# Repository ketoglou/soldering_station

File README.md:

# Soldering_station
A personal soldering station for Hakko 907 in Greek language but it can be easily adapted to any language.\
The following image shows the Temperature(red line) vs Resistance(blue line) chart of Hakko 907.\
 \
The equation that is used to calculate temperature is based in least squares method and \
it is the following : Temperature = 5.95 * Resistance - 281.3.

- PCB.zip : Contains gerber files for PCB.
- Firmware : Contains PIC18F27K42 firmware.

The following image shows the PCB.\

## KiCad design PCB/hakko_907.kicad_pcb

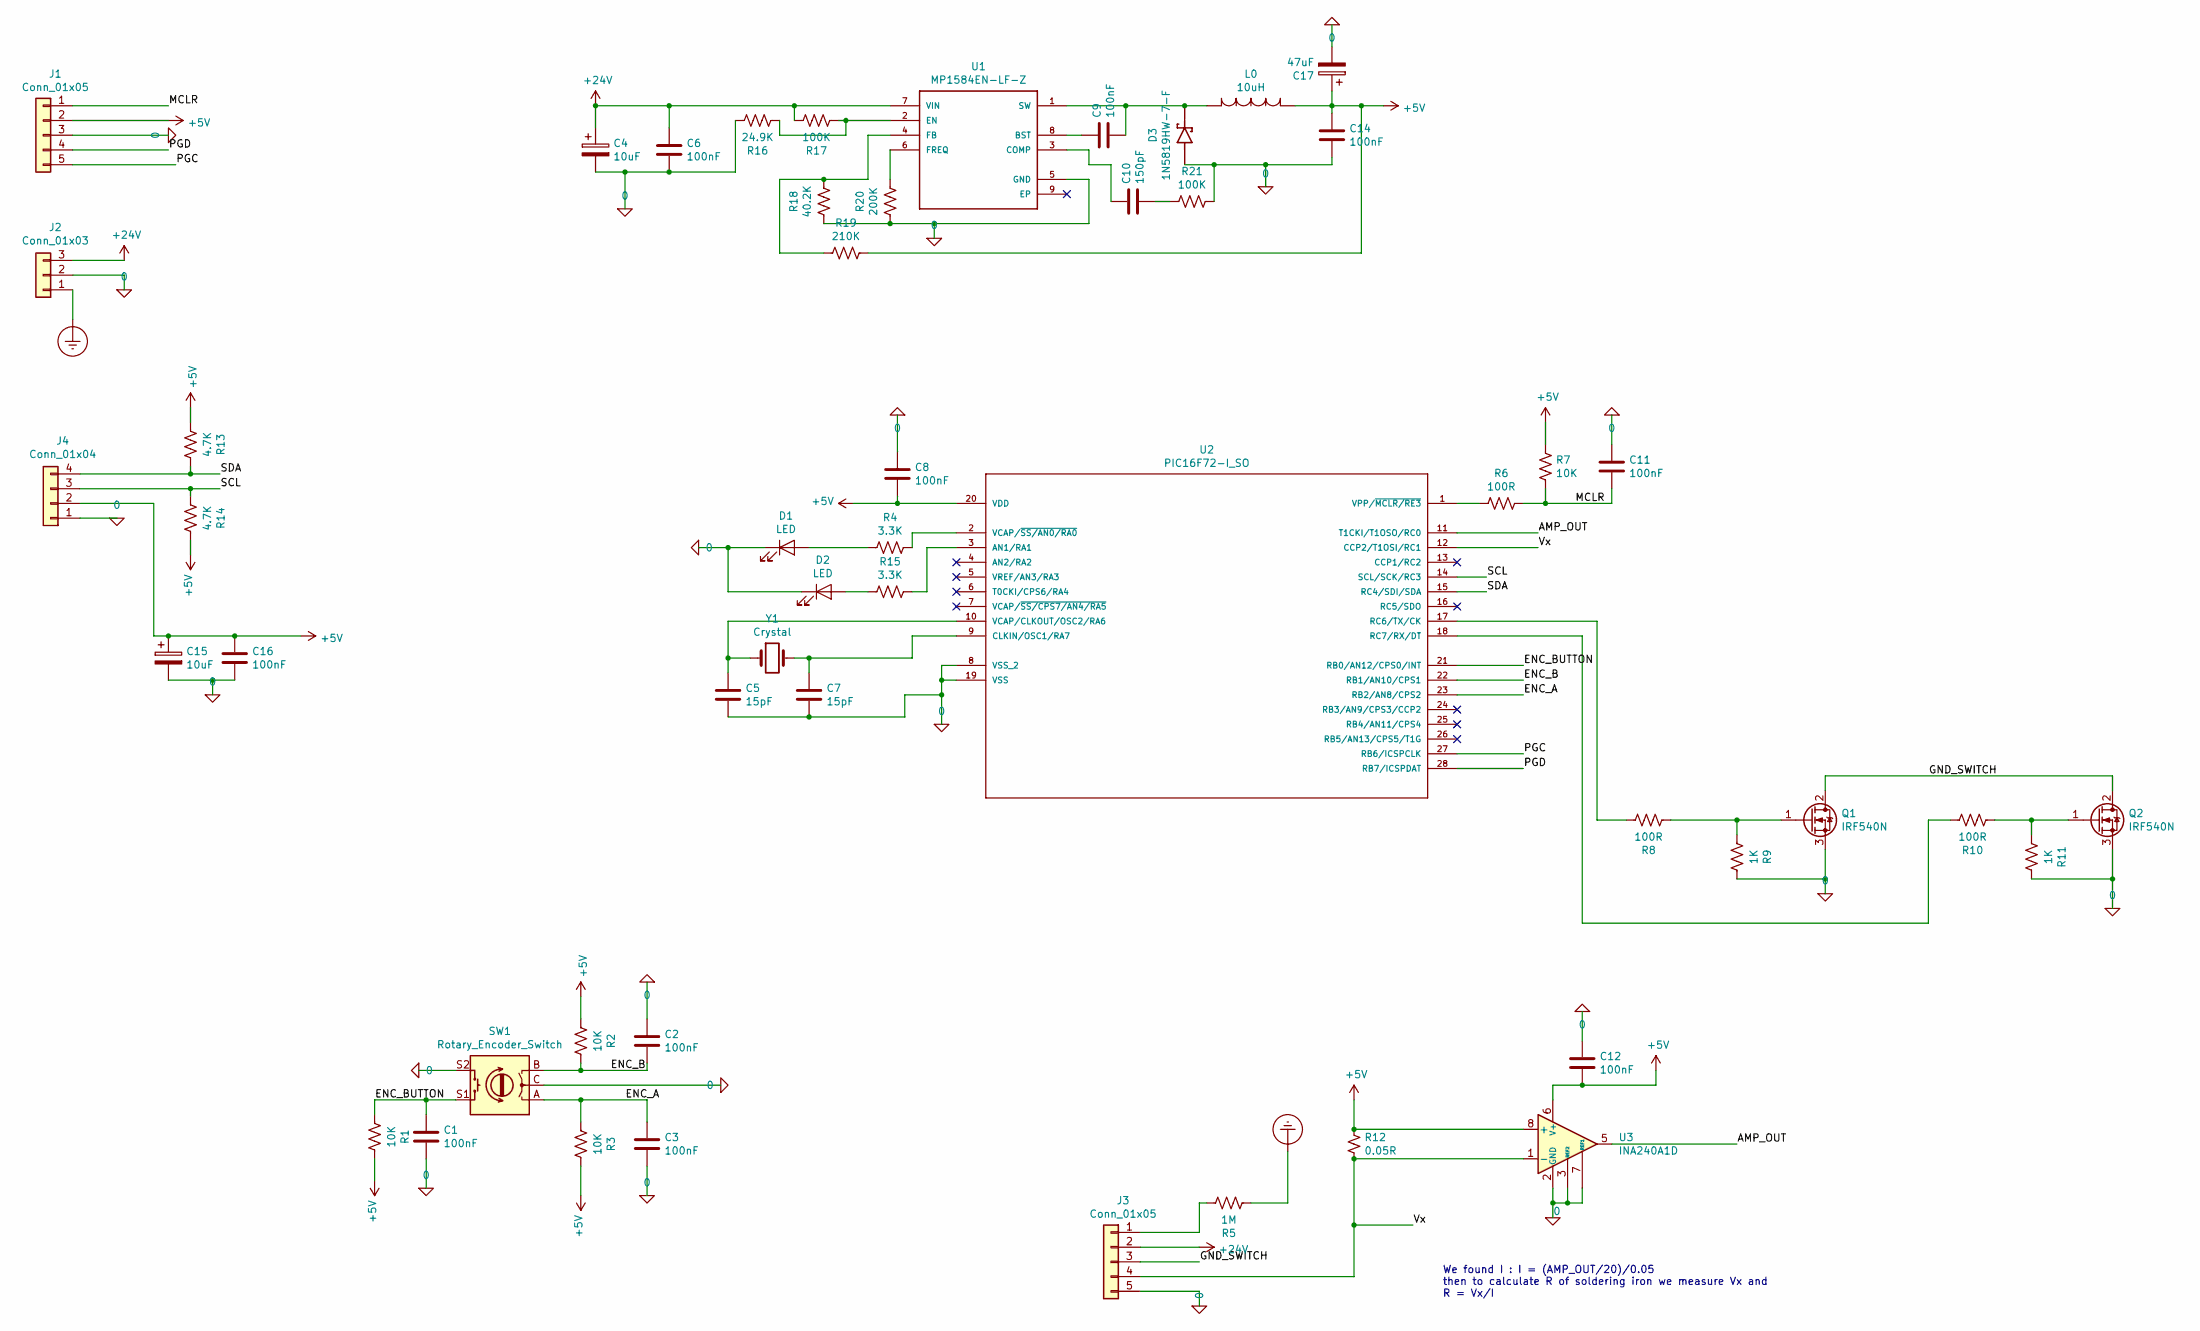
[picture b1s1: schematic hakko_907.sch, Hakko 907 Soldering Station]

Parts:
C1, C2, C3, C6, C8, C9, C11, C12, C14, C16: 100nF; C_0603_1608Metric_Pad1.05x0.95mm_HandSolder
C4, C15: 10uF; CP_Elec_8x6.2
C5, C7: 15pF; C_0603_1608Metric_Pad1.05x0.95mm_HandSolder
C10: 150pF; C_0603_1608Metric_Pad1.05x0.95mm_HandSolder
C17: 47uF; CP_Elec_6.3x5.9
D1, D2: LED; LED_0603_1608Metric_Pad1.05x0.95mm_HandSolder
D3: 1N5819HW-7-F; SOD3715X145N
J1, J3: Conn_01x05; PinHeader_1x05_P2.54mm_Vertical
J2: Conn_01x03; PinHeader_1x03_P2.54mm_Vertical
J4: Conn_01x04; PinHeader_1x04_P2.54mm_Vertical
L0: 10uH; INDM7676X355N
Q1, Q2: IRF540N; TO-220-3_Vertical
R1, R2, R3, R7: 10K; R_0603_1608Metric_Pad1.05x0.95mm_HandSolder
R4, R15: 3.3K; R_0603_1608Metric_Pad1.05x0.95mm_HandSolder
R5: 1M; R_Axial_DIN0309_L9.0mm_D3.2mm_P20.32mm_Horizontal
R6, R8, R10: 100R; R_0603_1608Metric_Pad1.05x0.95mm_HandSolder
R9, R11: 1K; R_0603_1608Metric_Pad1.05x0.95mm_HandSolder
R12: 0.05R; R_2512_6332Metric_Pad1.52x3.35mm_HandSolder
R13, R14: 4.7K; R_0603_1608Metric_Pad1.05x0.95mm_HandSolder
R16: 24.9K; R_0603_1608Metric_Pad1.05x0.95mm_HandSolder
R17, R21: 100K; R_0603_1608Metric_Pad1.05x0.95mm_HandSolder
R18: 40.2K; R_0603_1608Metric_Pad1.05x0.95mm_HandSolder
R19: 210K; R_0603_1608Metric_Pad1.05x0.95mm_HandSolder
R20: 200K; R_0603_1608Metric_Pad1.05x0.95mm_HandSolder
SW1: Rotary_Encoder_Switch; RotaryEncoder_Alps_EC11E-Switch_Vertical_H20mm
U1: MP1584EN-LF-Z; SOIC127P600X170-9N
U2: PIC16F72-I_SO; SOIC127P1030X265-28N
U3: INA240A1D; SOIC-8_3.9x4.9mm_P1.27mm
Y1: Crystal; Crystal_HC49-4H_Vertical

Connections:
0: C1.2, C2.1, C3.2, C4.2, C5.2, C6.2, C7.2, C8.1, C11.1, C12.1, C14.2, C15.2, C16.2, C17.2, D1.1 (K), D2.1 (K), D3.A, J1.3, J2.2, J3.5, J4.1, Q1.3 (S), Q2.3 (S), R9.1, R11.1, R16.1, R18.2, R20.2, R21.1, SW1.C, SW1.S2, U1.5 (GND), U2.8 (VSS_2), U2.19 (VSS), U3.2 (GND), U3.3 (REF2), U3.4 (GND), U3.7 (REF1)
+5V: C8.2, C12.2, C14.1, C15.1, C16.1, C17.1, J1.2, J4.2, L0.1, R1.1, R2.2, R3.1, R7.1, R12.1, R13.2, R14.1, R19.1, U2.20 (VDD), U3.6 (V+), U3.8 (+)
+24V: C4.1, C6.1, J2.3, J3.2, R17.1, U1.7 (VIN)
/AMP_OUT: U2.11 (T1CKI/T1OSO/RC0), U3.5
/ENC_A: C3.1, R3.2, SW1.A, U2.23 (RB2/AN8/CPS2)
/ENC_B: C2.2, R2.1, SW1.B, U2.22 (RB1/AN10/CPS1)
/ENC_BUTTON: C1.1, R1.2, SW1.S1, U2.21 (RB0/AN12/CPS0/INT)
/GND_SWITCH: J3.3, Q1.2 (D), Q2.2 (D)
/MCLR: C11.2, J1.1, R6.1, R7.2
/PGC: J1.5, U2.27 (RB6/ICSPCLK)
/PGD: J1.4, U2.28 (RB7/ICSPDAT)
/SCL: J4.3, R14.2, U2.14 (SCL/SCK/RC3)
/SDA: J4.4, R13.1, U2.15 (RC4/SDI/SDA)
/Vx: J3.4, R12.2, U2.12 (CCP2/T1OSI/RC1), U3.1 (-)
Earth_Protective: J2.1, R5.2
unnamed: C5.1, U2.10 (VCAP/CLKOUT/OSC2/RA6), Y1.1
unnamed: C7.1, U2.9 (CLKIN/OSC1/RA7), Y1.2
unnamed: C9.1, U1.8 (BST)
unnamed: C9.2, D3.C (K), L0.2, U1.1 (SW)
unnamed: C10.1, U1.3 (COMP)
unnamed: C10.2, R21.2
unnamed: D1.2 (A), R4.2
unnamed: D2.2 (A), R15.2
unnamed: J3.1, R5.1
unnamed: Q1.1 (G), R8.2, R9.2
unnamed: Q2.1 (G), R10.2, R11.2
unnamed: R4.1, U2.2 (VCAP/~SS/AN0/RA0)
unnamed: R6.2, U2.1 (VPP/~MCLR/RE3)
unnamed: R8.1, U2.17 (RC6/TX/CK)
unnamed: R10.1, U2.18 (RC7/RX/DT)
unnamed: R15.1, U2.3 (AN1/RA1)
unnamed: R16.2, R17.2, U1.2 (EN)
unnamed: R18.1, R19.2, U1.4 (FB)
unnamed: R20.1, U1.6 (FREQ)

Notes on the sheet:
We found I : I = (AMP_OUT/20)/0.05 then to calculate R of soldering iron we measure Vx and R = Vx/I

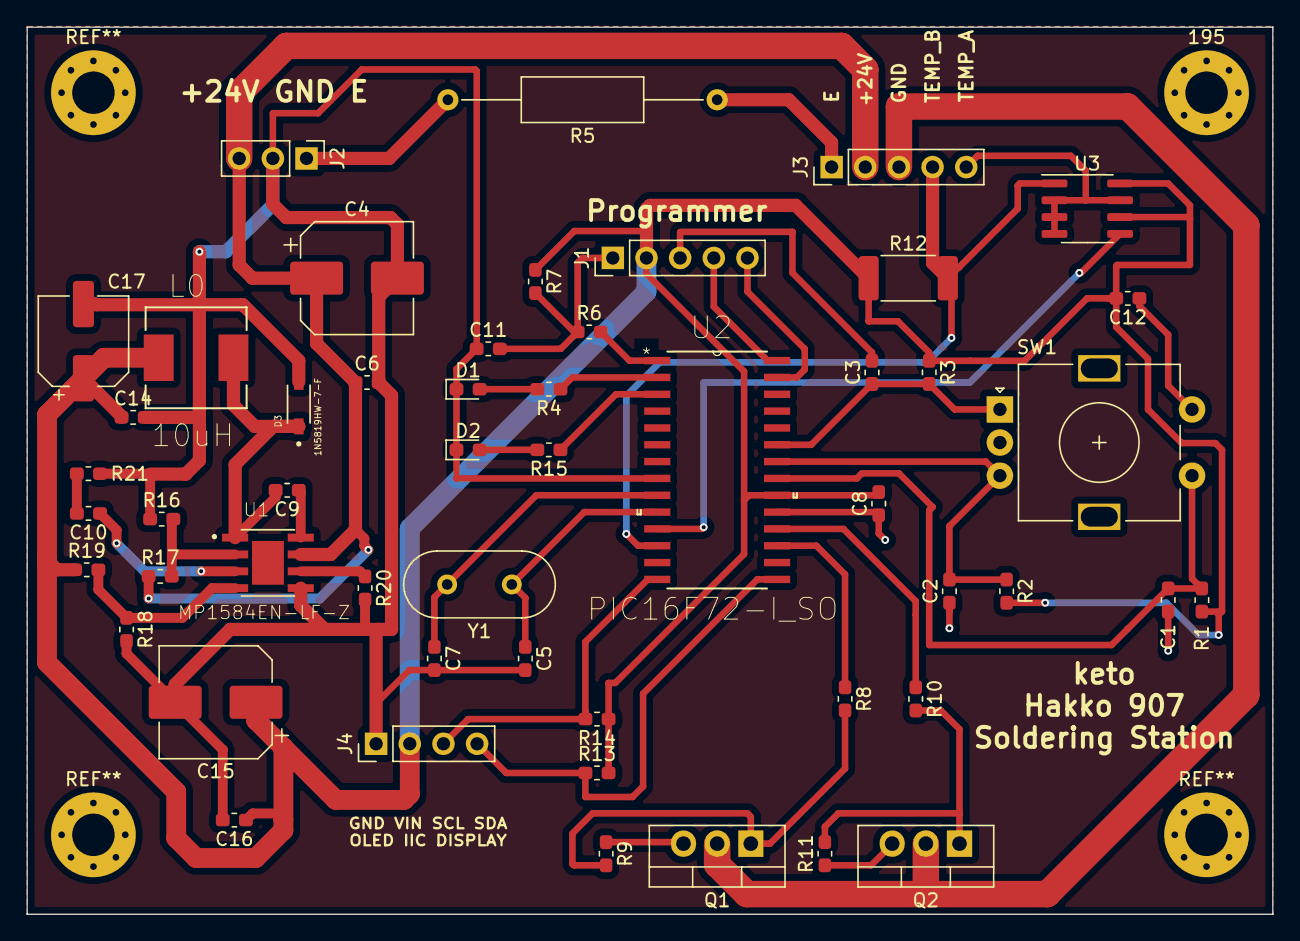
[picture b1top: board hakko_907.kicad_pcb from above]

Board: 2 copper layers, 94.0 x 66.9 mm, 53 parts (0 on the bottom side), 34 nets.

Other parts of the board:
195: MountingHole_3.2mm_M3_Pad_Via

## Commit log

2019-10-26 SSH907
